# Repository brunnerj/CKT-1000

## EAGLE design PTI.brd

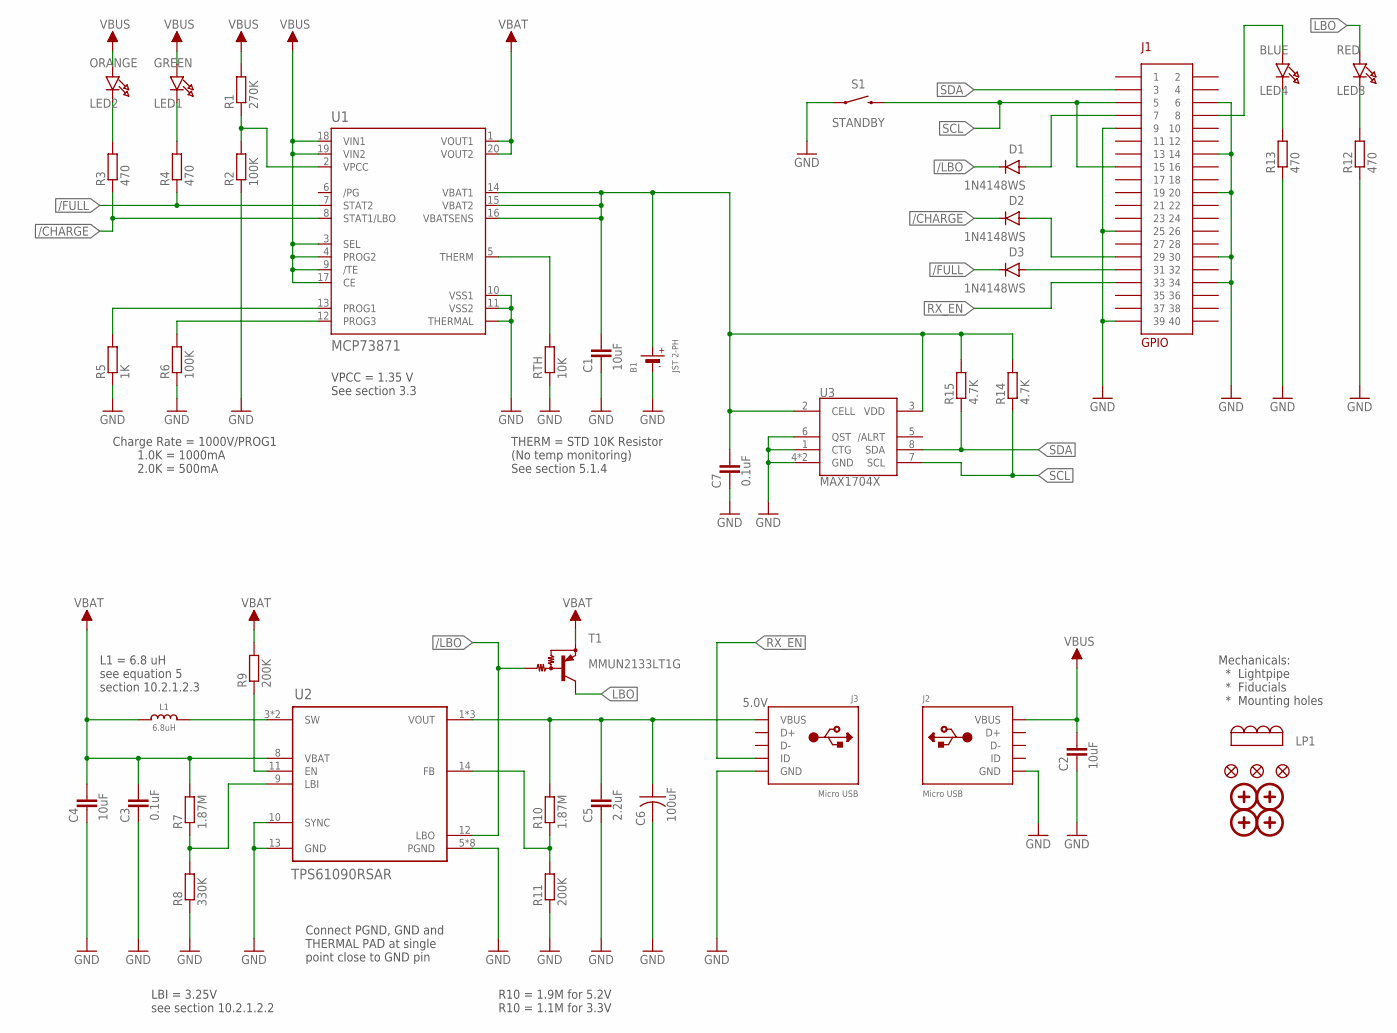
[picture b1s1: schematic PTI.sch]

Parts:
B1: JST 2-PH; JSTPH2
C1, C2, C4: 10uF; C0805
C3, C7: 0.1uF; C0805
C5: 2.2uF; C0805
C6: 100uF; C1210
D1, D2, D3: 1N4148WS; SOD-323
FID1, FID2, FID3: FIDUCIAL""; FIDUCIAL_1MM
J1: GPIO; HEADER-FE-2X20-TH
J2, J3: Micro USB; AMPHENOL_10103594
L1: 6.8uH; INDUCTOR_5X5MM_TDK_VLC5045
LED1: GREEN; CHIPLED_0805_NOOUTLINE
LED2: ORANGE; CHIPLED_0805_NOOUTLINE
LED3: RED; CHIPLED_0805_NOOUTLINE
LED4: BLUE; CHIPLED_0805_NOOUTLINE
LP1: LIGHTPIPE; LIGHTPIPE_QUAD_VERT_3MM
MH1, MH2, MH3, MH4: MOUNTING-HOLES; MOUNTING-HOLE-2.75X3MM
R1: 270K; R0805
R2, R6: 100K; R0805
R3, R4, R12, R13: 470; R0805
R5: 1K; R0805
R7, R10: 1.87M; R0805
R8: 330K; R0805
R9, R11: 200K; R0805
R14, R15: 4.7K; R0805
RTH: 10K; R0805
S1: STANDBY; TACTILE_SWITCH_PTH_12MM
T1: MMUN2133LT1G; SC59-BEC
U1: MCP73871; QFN20_4MM
U2: TPS61090RSAR; RSA16_4MMX4MM_VQFN
U3: MAX1704X; TDFN-8

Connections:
5.0V: C5.1, C6.1, J3.VBUS, R10.2, U2.1 (VOUT), U2.15 (VOUT), U2.16 (VOUT)
/CHARGE: D2.C, R3.1, U1.8 (STAT1/LBO)
/FULL: D3.C, R4.1, U1.7 (STAT2)
/LBO: D1.C, T1.B, U2.12 (LBO)
GND: B1.1 (-), B1.NC1 (-), B1.NC2 (-), C1.2, C2.2, C3.2, C4.2, C5.2, C6.2, C7.2, J1.P$6 (6), J1.P$9 (9), J1.P$14 (14), J1.P$20 (20), J1.P$25 (25), J1.P$30 (30), J1.P$34 (34), J1.P$39 (39), J2.BASE@1 (GND), J2.BASE@2 (GND), J2.GND, J2.SPRT@1 (GND), J2.SPRT@2 (GND), J2.SPRT@3 (GND), J2.SPRT@4 (GND), J3.BASE@1 (GND), J3.BASE@2 (GND), J3.GND, J3.SPRT@1 (GND), J3.SPRT@2 (GND), J3.SPRT@3 (GND), J3.SPRT@4 (GND), R2.1, R5.1, R6.1, R8.1, R11.1, R12.1, R13.1, RTH.1, S1.1, U1.10 (VSS1), U1.11 (VSS2), U1.P$21 (THERMAL), U1.P$22 (THERMAL), U1.P$23 (THERMAL), U1.P$24 (THERMAL), U2.5 (PGND), U2.6 (PGND), U2.7 (PGND), U2.10 (SYNC), U2.13 (GND), U2.P$17 (PGND), U2.P$18 (PGND), U2.P$19 (PGND), U2.P$20 (PGND), U2.P$21 (PGND), U3.1 (CTG), U3.4 (GND), U3.6 (QST), U3.EP (GND)
LBO: LED3.A, T1.C
unnamed: RTH.2, U1.5 (THERM)
unnamed: R1.1, R2.2, U1.2 (VPCC)
unnamed: D1.A, J1.P$7 (7)
unnamed: D2.A, J1.P$29 (29)
unnamed: R5.2, U1.13 (PROG1)
unnamed: R6.2, U1.12 (PROG3)
unnamed: LED2.C, R3.2
unnamed: LED1.C, R4.2
unnamed: B1.2 (+), C1.1, C7.1, R14.2, R15.2, U1.14 (VBAT1), U1.15 (VBAT2), U1.16 (VBATSENS), U3.2 (CELL), U3.3 (VDD)
unnamed: L1.P$2 (2), U2.3 (SW), U2.4 (SW)
unnamed: R7.1, R8.2, U2.9 (LBI)
unnamed: R9.1, U2.11 (EN)
unnamed: R10.1, R11.2, U2.14 (FB)
unnamed: LED3.C, R12.2
unnamed: D3.A, J1.P$31 (31)
unnamed: LED4.C, R13.2
RX_EN: J1.P$33 (33), J3.ID
SCL: J1.P$5 (5), J1.P$15 (15), R14.1, S1.3 (2), U3.7 (SCL)
SDA: J1.P$3 (3), R15.1, U3.8 (SDA)
STATUS: J1.P$8 (8), LED4.A
VBAT: C3.1, C4.1, L1.P$1 (1), R7.2, R9.2, T1.E, U1.1 (VOUT1), U1.20 (VOUT2), U2.8 (VBAT)
VBUS: C2.1, J2.VBUS, LED1.A, LED2.A, R1.2, U1.3 (SEL), U1.4 (PROG2), U1.9 (/TE), U1.17 (CE), U1.18 (VIN1), U1.19 (VIN2)

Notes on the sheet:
Charge Rate = 1000V/PROG1 1.0K = 1000mA 2.0K = 500mA
THERM = STD 10K Resistor (No temp monitoring) See section 5.1.4
VPCC = 1.35 V See section 3.3
Connect PGND, GND and THERMAL PAD at single point close to GND pin
R10 = 1.9M for 5.2V R10 = 1.1M for 3.3V
LBI = 3.25V see section 10.2.1.2.2
L1 = 6.8 uH see equation 5 section 10.2.1.2.3
Mechanicals: * Lightpipe * Fiducials * Mounting holes

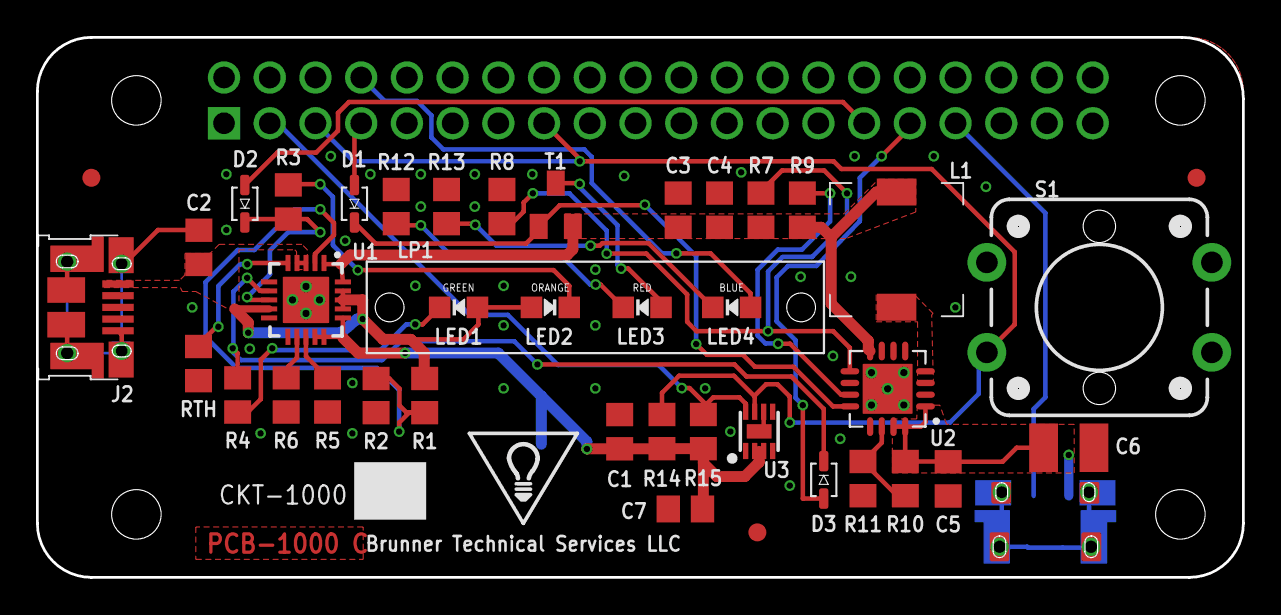
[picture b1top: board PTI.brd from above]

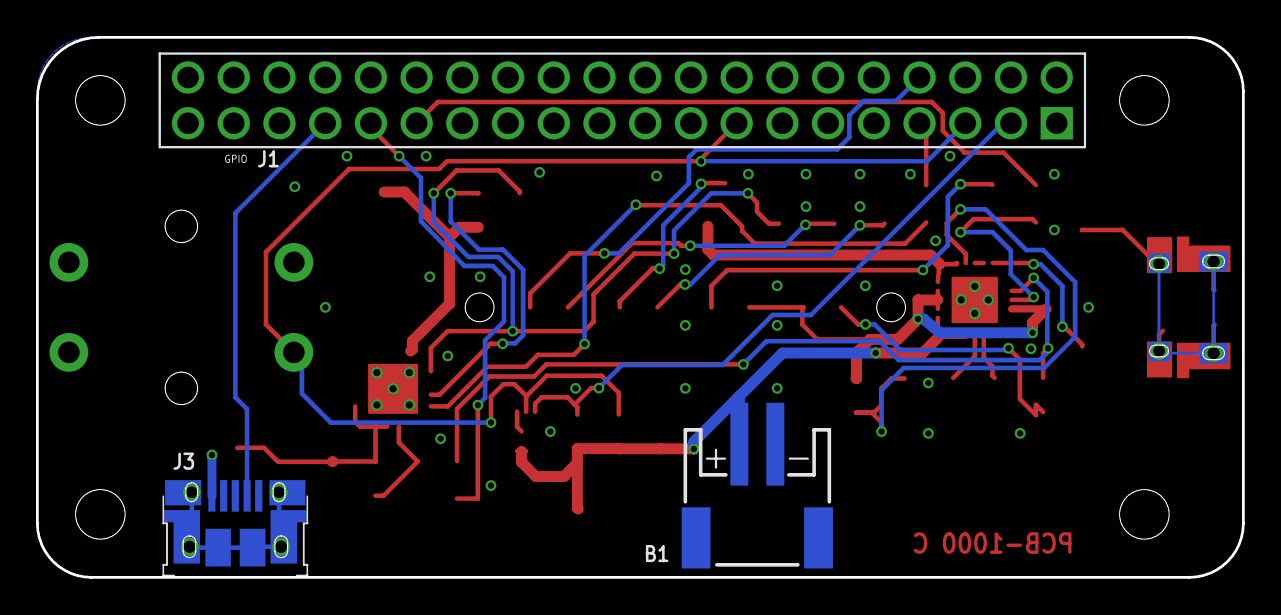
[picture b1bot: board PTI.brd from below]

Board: 2 copper layers, 67.0 x 30.0 mm, 48 parts (3 on the bottom side), 28 nets.

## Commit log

2019-08-28 initial commit - rev A
2019-08-30 Rev B adds 2mm to the left side of the board to facilitate USB connections.
2019-11-04 Routes GPIO13 (pin 33 on J1) to the ID pin on J3 (power out to USB manifold). This GPIO can be used to toggle on/off a MOSFET on the USB manifold used to enable or disable receiver 5V power bus.
